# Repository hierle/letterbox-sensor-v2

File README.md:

# LoRaWan EU868MHz Letterbox Sensor v2
sensing letters in your letterbox via two infrared proximity sensors (HSDL9100),
sending out status via lora / lorawan, using RAK3172 (based on STM32WLE5CC) CPU/RF, powered by a CR2032 battery.

<br>

This project was inspired by the heise ct briefkasten sensor project<br>
https://www.heise.de/ratgeber/IoT-Netz-LoRaWAN-Briefkastensensor-mit-hoher-Reichweite-selber-bauen-4417179.html<br>
https://github.com/jamct/radio-mailbox<br>
and is a direct successor of version 1: https://github.com/hierle/letterbox-sensor

Contents:
- ./PCB/ :                  kicad PCB files
- ./letterbox-sensor-v2/ :  lorawan letterbox sensor sketch
- ./misc/ :                 payload decoder, sample http integration cgi

An extended web ui by Peter is available here: https://github.com/pbiering/letterbox-sensor-web

A nice alternative software by Henrik, using Lora P2P mode is available here: https://github.com/HonkStonk/MightyMailbox

Compiled and flashed with ArduinoIDE with RAKWireless STM32 extensions

Features:
- using RAKWireless RAK3172 based on STM32WLE5CC
- deep sleep at (measured) 5uA including battery voltage divider and tantalium caps
- two proximity sensors HSDL9100
- USB-C interface for flashing and serial monitor, via FT230XS-R USB-UART
- onboard 868MHz PCB antenna after TI document http://www.ti.com/lit/an/swra227e/swra227e.pdf
- lorawan activation either ABP or OTAA
- battery voltage measurment thru voltage divider (2x 10MOhm)

Changes to v1:
- replaced ATTiny and RFM95 with RAK3172, much more CPU power and memory, much simpler code
- support for OTAA lorawan activation
- much simpler software stack, using ArduinoIDE with RAKWireless STM32 extensions and API usage
- added USB-C interface, no more special programming interface needed
- added second HSDL9100 for better physical letterbox coverage
- added two (optional) supporting tantalium caps for extended battery life
- removed temperature, as not easily avail on STM32WLE5CC / RAK API
- removed trimmers

BOM (digikey.de):

| Count | Part number        | Description             | Usage                    |
|-------|--------------------|-------------------------|--------------------------|
| 1     | RAK3172-8-SM-NI    | CPU/RF-Lora  NO IPEX!   | CPU/RF module            |
| 2     | CS1213AGF260       | Tactile switch          | Boot/Reset               |
| 2     | HSDL-9100-021/024  | Proximity Sensor        | Proximity sensors        |
| 2     | CRGCQ1206F33R      | RES 33 Ohm 1206         | Proximity sens LED       | 
| 2     | CRGCQ1206F1M0      | RES 1M Ohm 1206         | Proximity sens diode     |
| 1     | BU2032SM-FH-GTR    | CR2032 COIN CELL HOLDER | Battery                  |
| 2     | TAJE477M010RNJ     | CAP tant 470u           | Battery supporting caps  |
| 1     | LQG18HN1N8S00D     | IND 1.8NH 0603          | Antenna matching         |
| 1     | GRM1885C1H2R7CA01D | CAP 2.7PF 0603          | Antenna matching         |
| 3     | GRM188R72A104KA35D | CAP CER 0.1u 0603       | Suppressor caps          |
| 2     | GRM188D71A106KA73D | CAP CER 10u 0603        | Suppressor caps          |
| 1     | RAHUC31AUTR        | USB-C connector         | USB                      |
| 1     | FT230XS-R          | FTDI USB Serial UART    | USB UART                 |
| 1     | MI0805K601R-10     | Ferrite bead 0805       | USB power                |
| 2     | AC1206FR-075K1L    | RES 5.1k Ohm 1206       | USB power sens           |
| 2     | CRGCQ1206F22R      | RES 22 Ohm 1206         | USB lines                |
| 1     | GRM188R72A104KA35D | DIP switch              | Power switch USB/Battery |
| 2     | AA3528LSECKT/J4    | LED orange              | Status/USB status        |
| 2     | CRGCQ1206F220R     | RES 220 Ohm 1206        | Status LEDs              |
| 2     | RC1206FR-0710ML    | RES 10M Ohm 1206        | Battery voltage measure  |

RAK3172 documentation:

https://docs.rakwireless.com/Product-Categories/WisDuo/RAK3172-Module/Overview/

How to compile:

Follow the instructions on<br>
https://docs.rakwireless.com/Product-Categories/WisDuo/RAK3172-Module/Quickstart/<br>
in short:<br>
- install ArduinoIDE from arduino.cc
- add the following URL to the boards manager URLs section in preferences:
https://raw.githubusercontent.com/RAKWireless/RAKwireless-Arduino-BSP-Index/main/package_rakwireless.com_rui_index.json
- install the "RAKwireless RUI STM32 Boards" from the Boards Manager
- select "WisDuo RAK3172 Evaluation Board" board
- on Mac you might need to install pyserial: sudo pip3 install pyserial
- on Linux you might need to install python3-pyserial
- connect the board, make sure it's powered on (DIP switch)
- select the corresponding serial port
- open the sketch folder
- adjust config.h and lorawan.h
- compile and flash

For configuration adjust config.h and lorawan.h

config.h:
- PERIOD: the time intervall you want the sensor to send it's data, in minutes, default is 30 minutes
- THRESHOLD: the threshold for the sensor readings (empty/full), can later be "overwritten" in e.g. HTML integration
- USE_OTAA: if true, OTAA will be used instead of ABP, so we do not have to worry about frame counters after reset / battery change
- DATARATE and TXPOWER: adjust to your needs, your packets should be reliably received, w/o wasting to much power
- see also the comments for each entry in config.h

lorawan.h:
- set your lorawan keys for either ABP or OTAA
- OTAA_APPEUI or JOINEUI is only needed to select a specific JOIN server, in private networks can be set to any value

Additional notes:
- you will need a *DATA* USB-C cable, a charging only cable will not work, as it's missing the data pins ;-)
- the DIP switch allows to power the device directly from USB, but when using the battery in production environment (letterbox), it should be switched off, not to waist power on the FT230 USB-UART chip

Letterbox sensor v2 lorawan payload package byte structure:

|byte|    0     |  1   2 | 3   4 | 5   6 |    7    |
|----|----------|--------|-------|-------|---------|
|    |0x00=empty|battery |sensor1|sensor2|threshold|
|    |0xFF=full |voltage |raw    |raw    |         |

Todos:
- read battery voltage and temperature from STM32
- see sections 3.18.1 and 3.18.3 in: https://www.st.com/resource/en/datasheet/stm32wle5c8.pdf

Have fun!

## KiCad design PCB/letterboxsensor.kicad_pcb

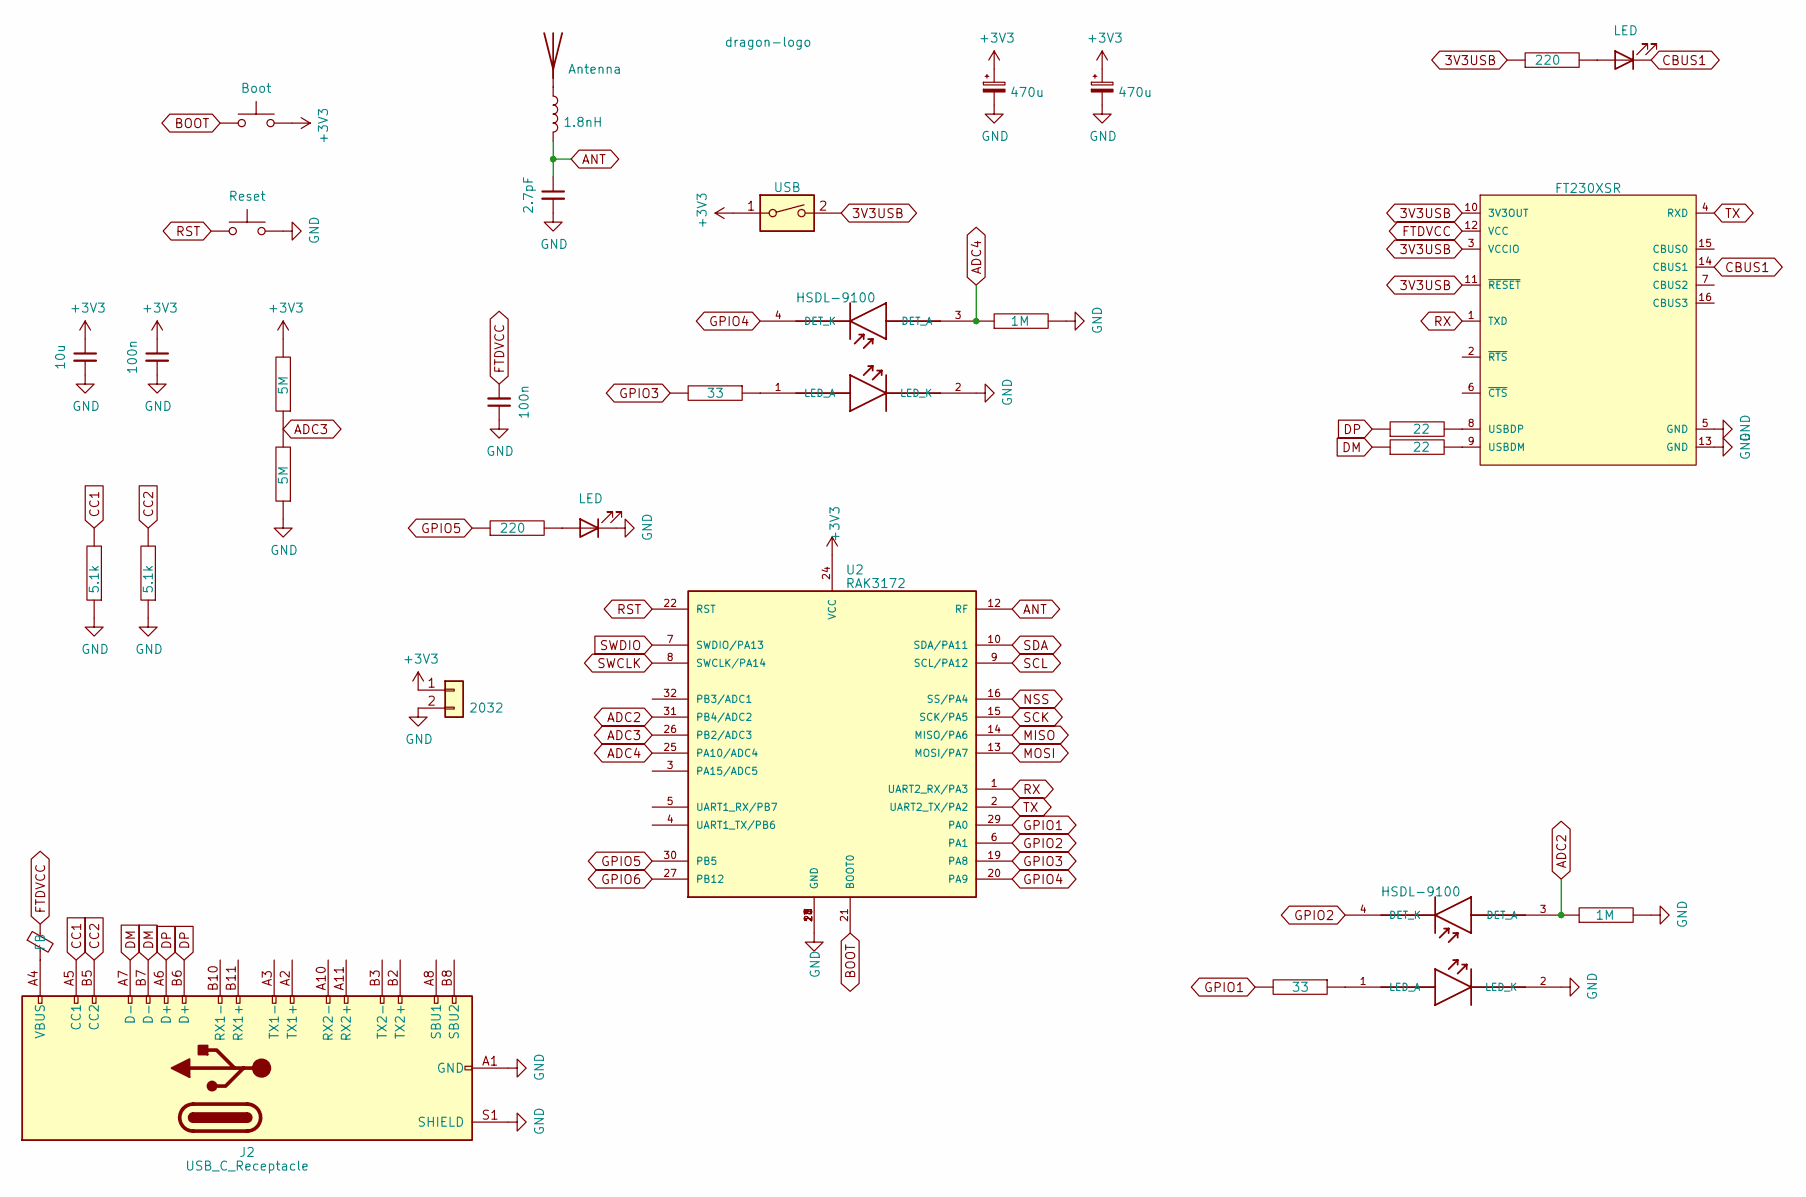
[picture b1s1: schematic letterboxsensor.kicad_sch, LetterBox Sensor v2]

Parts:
AE1: Antenna; TI-DN024-SL-SHORT
C1: 2.7pF; C_0603_1608Metric_Pad1.08x0.95mm_HandSolder
C2, C3: 470u; CP_EIA-7343-30_AVX-N_Pad2.25x2.55mm_HandSolder
C4, C7: 100n; C_0603_1608Metric_Pad1.08x0.95mm_HandSolder
C5: 10u; C_0603_1608Metric_Pad1.08x0.95mm_HandSolder
D1, D3: HSDL-9100; Broadcom-HSDL-9100-021-0-0-MFG
D2, D4: LED; LED_PLCC_2835_Handsoldering
DRAGON2: dragon-logo; Dragon
FB1: FB; L_0805_2012Metric_Pad1.05x1.20mm_HandSolder
J1: 2032; BatteryHolder_MPD_BU2032SM-FH_2032
J2: USB_C_Receptacle; USB_C_Receptacle_RAHUC31AUTR
JP1: USB; SW_DIP_SPSTx01_Slide_Omron_A6S-110x_W8.9mm_P2.54mm
L1: 1.8nH; L_0603_1608Metric
R1, R5: 33; R_1206_3216Metric
R2, R8: 220; R_1206_3216Metric
R4, R7: 1M; R_1206_3216Metric
R9, R10: 5.1k; R_1206_3216Metric
R11, R14: 5M; R_1206_3216Metric
R12, R13: 22; R_1206_3216Metric
SW1: Boot; SW_Push_SPST_NO_Alps_SKRK
SW2: Reset; SW_Push_SPST_NO_Alps_SKRK
U2: RAK3172
U3: FT230XSR; FTDI-SSOP-16-0-0-IPC_A; mouser part number 895-FT230XS-R; digikey description IC USB SERIAL BASIC UART 16SSOP

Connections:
3V3USB: JP1.2, R8.1, U3.3 (VCCIO), U3.10 (3V3OUT), U3.11 (~RESET)
+3V3: C2.1, C3.1, C4.1, C5.1, J1.1, JP1.1, R11.2, SW1.2, U2.24 (VCC)
ADC2: D3.3 (DET_A), R7.1, U2.31 (PB4/ADC2)
ADC3: R11.1, R14.2, U2.26 (PB2/ADC3)
ADC4: D1.3 (DET_A), R4.1, U2.25 (PA10/ADC4)
ANT: C1.1, L1.2, U2.12 (RF)
BOOT: SW1.1, U2.21 (BOOT0)
CBUS1: D4.1 (K), U3.14 (CBUS1)
CC1: J2.A5 (CC1), R10.2
CC2: J2.B5 (CC2), R9.2
DM: J2.A7 (D-), J2.B7 (D-), R13.1
DP: J2.A6 (D+), J2.B6 (D+), R12.1
FTDVCC: C7.2, FB1.1, U3.12 (VCC)
GND: C1.2, C2.2, C3.2, C4.2, C5.2, C7.1, D1.2 (LED_K), D2.1 (K), D3.2 (LED_K), J1.2, J2.A1 (GND), J2.A12 (GND), J2.B1 (GND), J2.B12 (GND), J2.S1 (SHIELD), R4.2, R7.2, R9.1, R10.1, R14.1, SW2.2, U2.11 (GND), U2.17 (GND), U2.18 (GND), U2.23 (GND), U2.28 (GND), U3.5 (GND), U3.13 (GND)
GPIO1: R5.2, U2.29 (PA0)
GPIO2: D3.4 (DET_K), U2.6 (PA1)
GPIO3: R1.2, U2.19 (PA8)
GPIO4: D1.4 (DET_K), U2.20 (PA9)
GPIO5: R2.1, U2.30 (PB5)
GPIO6: U2.27 (PB12)
MISO: U2.14 (MISO/PA6)
MOSI: U2.13 (MOSI/PA7)
NSS: U2.16 (SS/PA4)
unnamed: AE1.1 (A), L1.1
unnamed: D1.1 (LED_A), R1.1
unnamed: D2.2 (A), R2.2
unnamed: D3.1 (LED_A), R5.1
unnamed: D4.2 (A), R8.2
unnamed: FB1.2, J2.A4 (VBUS), J2.A9 (VBUS), J2.B4 (VBUS), J2.B9 (VBUS)
unnamed: R13.2, U3.9 (USBDM)
unnamed: R12.2, U3.8 (USBDP)
RST: SW2.1, U2.22 (RST)
RX: U2.1 (UART2_RX/PA3), U3.1 (TXD)
SCK: U2.15 (SCK/PA5)
SCL: U2.9 (SCL/PA12)
SDA: U2.10 (SDA/PA11)
SWCLK: U2.8 (SWCLK/PA14)
SWDIO: U2.7 (SWDIO/PA13)
TX: U2.2 (UART2_TX/PA2), U3.4 (RXD)

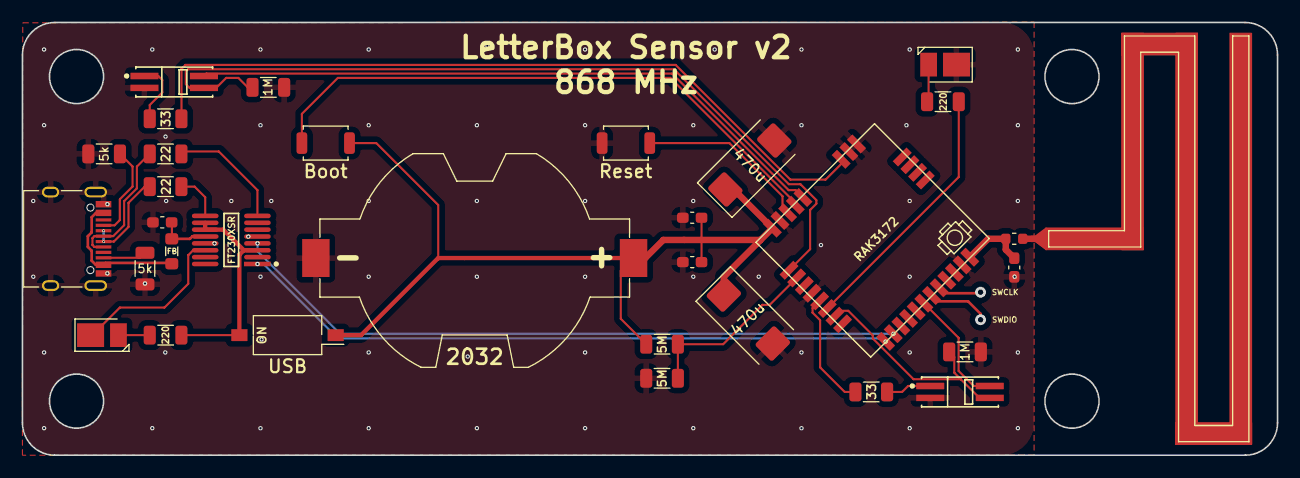
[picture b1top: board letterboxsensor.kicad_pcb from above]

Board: 2 copper layers, 116.0 x 40.0 mm, 33 parts (1 on the bottom side), 30 nets.

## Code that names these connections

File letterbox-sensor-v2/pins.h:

//
// pins.h
//

// pin mappings

// status led
#define statusled PB5

// sensor #1
// ir-led of proximity sensor#1 (invisible)
#define irled1 PA0
// power in for diode in proximity sensor
#define irdiode1 PA1
// adc pin (connect to output of sensor)
#define irsens1 PB4

// sensor #2
// ir-led of proximity sensor#1 (invisible)
#define irled2 PA8
// power in for diode in proximity sensor
#define irdiode2 PA9
// adc pin (connect to output of sensor)
#define irsens2 PA10

// adc pin battery voltage divider
#define vdiv PB2

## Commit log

2024-01-07 updated png
2024-01-07 updated lora package structure
2024-01-12 updated to 10MOhm voltage divider
2024-01-13 added 2nd picture
2024-01-18 added link to Peters web gui
2024-01-19 added hints about pyserial
2024-01-23 humanize PERIOD
2024-01-24 bugfix
2026-04-14 added link to Henriks P2P mode software
